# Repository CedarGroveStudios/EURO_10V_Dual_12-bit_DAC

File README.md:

# EURO_10V_Dual_12-bit_DAC
 A Stemma-powered dual 12-bit DAC Eurorack Module capable of producing +10V CV outputs.

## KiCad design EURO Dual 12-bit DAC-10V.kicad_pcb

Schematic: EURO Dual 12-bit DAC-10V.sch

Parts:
C1, C3: 22uF; C_0805
C2: 0.001uF; C_0805
D1: PANEL_PWR; Cedar_Grove_logo_lighted
J1: DAC00_OUT; Pin_Header_Straight_1x02_Pitch2.54mm_SMD_Pin1Right
J2: DAC01_OUT; Pin_Header_Straight_1x02_Pitch2.54mm_SMD_Pin1Right
J3: STEMMA JSP; JST_PH_S4B-PH-SM4-TB_04x2.00mm_Angled
L1: 22uH; NRH2410_inductor
R1, R3, R5, R6, R8: 10K; R_0805
R2, R4: 23.2K; R_0805
R7: 15K; R_0805
R9: 100m; R_0805
R10: 32.4K; R_0805
R11: 1K; R_0805
TD1: ZXTNS618MC; DFN-8_2x3mm_Pitch0.65mm_noEP
U1: TLV272
U2, U3: MCP4725A1T-E_CH; SOT-23-6_Handsoldering
U4: ZXSC410; SOT-23-6_Handsoldering

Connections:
+3V3: C1.1, J3.3, L1.1, R5.1, R6.1, R8.2, U2.3, U3.3, U3.6, U4.1
/SCL: J3.1, R6.2, U2.5, U3.5
/SDA: J3.2, R5.2, U2.4, U3.4
GND: C1.2, C3.2, D1.1, J1.2, J2.2, J3.4, R1.1, R3.2, R9.1, R11.1, U1.4 (V-), U2.2, U2.6, U3.2, U4.2
unnamed: C2.1, R10.1, R11.2, U4.5
unnamed: D1.2, R7.2
unnamed: J1.1, R2.2, U1.1
unnamed: J2.1, R4.1, U1.7
unnamed: L1.2, TD1.4, TD1.7, TD1.8
unnamed: R1.2, R2.1, U1.2 (-)
unnamed: R3.1, R4.2, U1.6 (-)
unnamed: R8.1, U4.3
unnamed: R9.2, TD1.2, U4.4
unnamed: TD1.1, U4.6
unnamed: U1.3 (+), U2.1
unnamed: U1.5 (+), U3.1
V+: C2.2, C3.1, R7.1, R10.2, TD1.5, TD1.6, U1.8 (V+)

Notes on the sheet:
POWER MGT
WHT
GRN
I2C:0x62 (98)
I2C:0x63 (99)
Output Buffer Gain = 1 + (23.2K/10K) = 3.3 3.3v --> 10v
JST S4B-SM4-TB or JST B4B-PH-K-S connector DigiKey 455-1751-1-ND or 455-1706-ND
Vout = Vfb (1 + ( R10 / R11 )) where Vfb = 0.3v 10 = 0.3 ( 1 + ( 32.3K / 1K ))

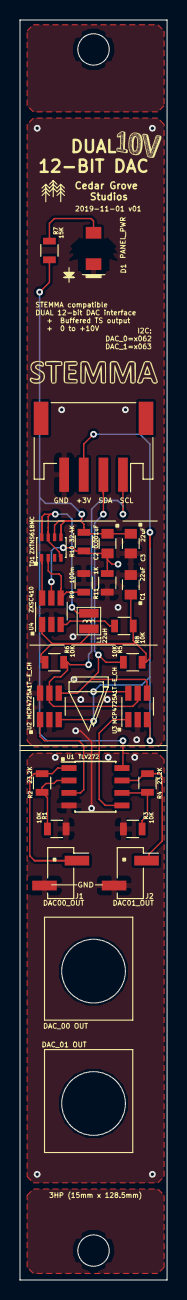
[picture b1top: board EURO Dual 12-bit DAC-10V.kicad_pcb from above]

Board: 2 copper layers, 15.0 x 128.5 mm, 26 parts (1 on the bottom side), 17 nets.

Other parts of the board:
DAC_00 OUT, DAC_01 OUT: MountingHole_6.5mm

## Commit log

2019-11-11 initial repo load
2019-11-11 Create LICENSE
